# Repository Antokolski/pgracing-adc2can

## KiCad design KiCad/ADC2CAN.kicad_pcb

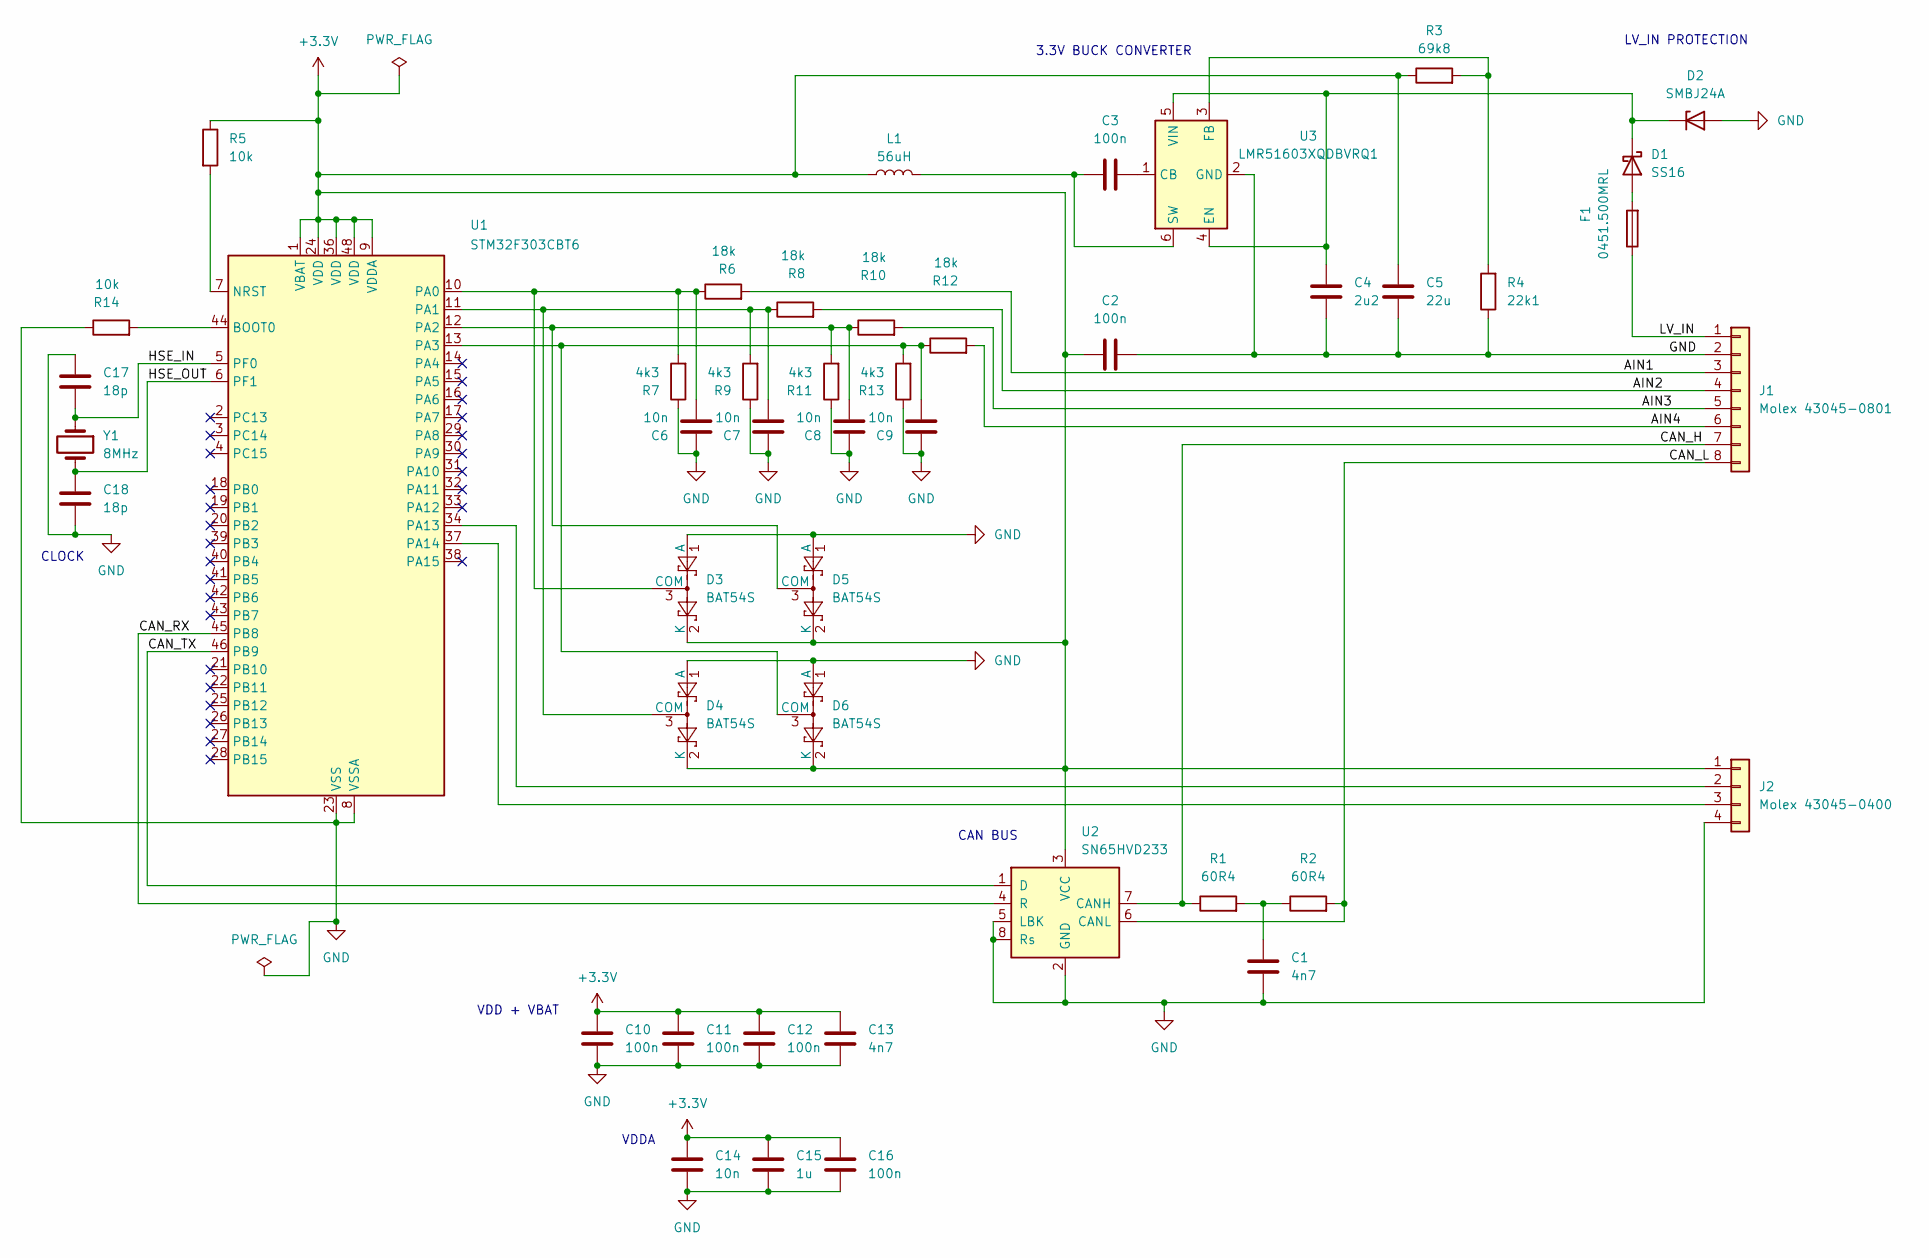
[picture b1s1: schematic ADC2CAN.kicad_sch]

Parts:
C1: 4n7; C_0603_1608Metric
C2, C3, C10, C11, C12, C16: 100n; C_0603_1608Metric
C4: 2u2; C_1206_3216Metric
C5: 22u; C_1210_3225Metric
C6, C7, C8, C9, C14: 10n; C_0603_1608Metric
C13: 4n7; C_0805_2012Metric
C15: 1u; C_0805_2012Metric
C17, C18: 18p; C_0603_1608Metric
D1: SS16; D_SMA
D2: SMBJ24A; D_SMB
D3, D4, D5, D6: BAT54S; SOT-23
F1: 0451.500MRL; Fuse_Littelfuse-NANO2-451_453
J1: Molex 43045-0801; Molex_Micro-Fit_3.0_43045-0800_2x04_P3.00mm_Horizontal
J2: Molex 43045-0400; Molex_Micro-Fit_3.0_43045-0400_2x02_P3.00mm_Horizontal
L1: 56uH; L_Bourns_SRN6045TA
R1, R2: 60R4; R_0603_1608Metric
R3: 69k8; R_0603_1608Metric
R4: 22k1; R_0603_1608Metric
R5, R14: 10k; R_0603_1608Metric
R6, R8, R10, R12: 18k; R_0603_1608Metric
R7, R9, R11, R13: 4k3; R_0603_1608Metric
U1: STM32F303CBT6; LQFP-48_7x7mm_P0.5mm
U2: SN65HVD233; SOIC-8_3.9x4.9mm_P1.27mm
U3: LMR51603XQDBVRQ1; SOT-23-6
Y1: 8MHz; Crystal_SMD_5032-2Pin_5.0x3.2mm

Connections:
+3.3V: C2.1, C5.1, C10.2, C11.2, C12.2, C13.1, C14.2, C15.2, C16.2, D3.2 (K), D4.2 (K), D5.2 (K), D6.2 (K), J2.1, L1.1, R3.1, R5.1, U1.1 (VBAT), U1.9 (VDDA), U1.24 (VDD), U1.36 (VDD), U1.48 (VDD), U2.3 (VCC)
/AIN1: J1.3, R6.2
/AIN2: J1.4, R8.2
/AIN3: J1.5, R10.2
/AIN4: J1.6, R12.2
/CAN_H: J1.7, R1.1, U2.7 (CANH)
/CAN_L: J1.8, R2.2, U2.6 (CANL)
/CAN_RX: U1.45 (PB8), U2.4 (R)
/CAN_TX: U1.46 (PB9), U2.1 (D)
/HSE_IN: C17.2, U1.5 (PF0), Y1.1
/HSE_OUT: C18.1, U1.6 (PF1), Y1.2
/LV_IN: F1.1, J1.1
GND: C1.2, C2.2, C4.2, C5.2, C6.1, C7.1, C8.1, C9.1, C10.1, C11.1, C12.1, C13.2, C14.1, C15.1, C16.1, C17.1, C18.2, D2.2 (A), D3.1 (A), D4.1 (A), D5.1 (A), D6.1 (A), J1.2, J2.4, R4.1, R7.1, R9.1, R11.1, R13.1, R14.1, U1.8 (VSSA), U1.23 (VSS), U1.35 (VSS), U1.47 (VSS), U2.2 (GND), U2.5 (LBK), U2.8 (Rs), U3.2 (GND)
unnamed: C1.1, R1.2, R2.1
unnamed: D1.2 (A), F1.2
unnamed: C4.1, D1.1 (K), D2.1 (K), U3.4 (EN), U3.5 (VIN)
unnamed: C6.2, D3.3 (COM), R6.1, R7.2, U1.10 (PA0)
unnamed: C7.2, D4.3 (COM), R8.1, R9.2, U1.11 (PA1)
unnamed: C8.2, D5.3 (COM), R10.1, R11.2, U1.12 (PA2)
unnamed: C9.2, D6.3 (COM), R12.1, R13.2, U1.13 (PA3)
unnamed: J2.2, U1.34 (PA13)
unnamed: J2.3, U1.37 (PA14)
unnamed: R14.2, U1.44 (BOOT0)
unnamed: R5.2, U1.7 (NRST)
unnamed: C3.2, U3.1 (CB)
unnamed: R3.2, R4.2, U3.3 (FB)
unnamed: C3.1, L1.2, U3.6 (SW)

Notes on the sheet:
VDD + VBAT
VDDA
CLOCK
LV_IN PROTECTION
CAN BUS
3.3V BUCK CONVERTER

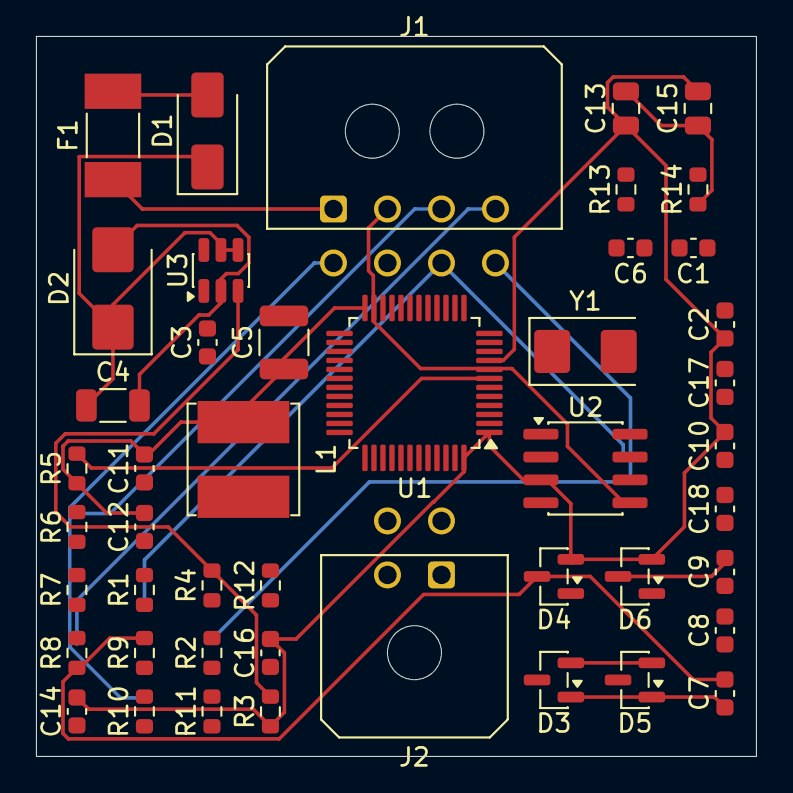
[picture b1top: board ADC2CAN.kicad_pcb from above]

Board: 4 copper layers, 40.0 x 40.0 mm, 46 parts (0 on the bottom side), 27 nets.
